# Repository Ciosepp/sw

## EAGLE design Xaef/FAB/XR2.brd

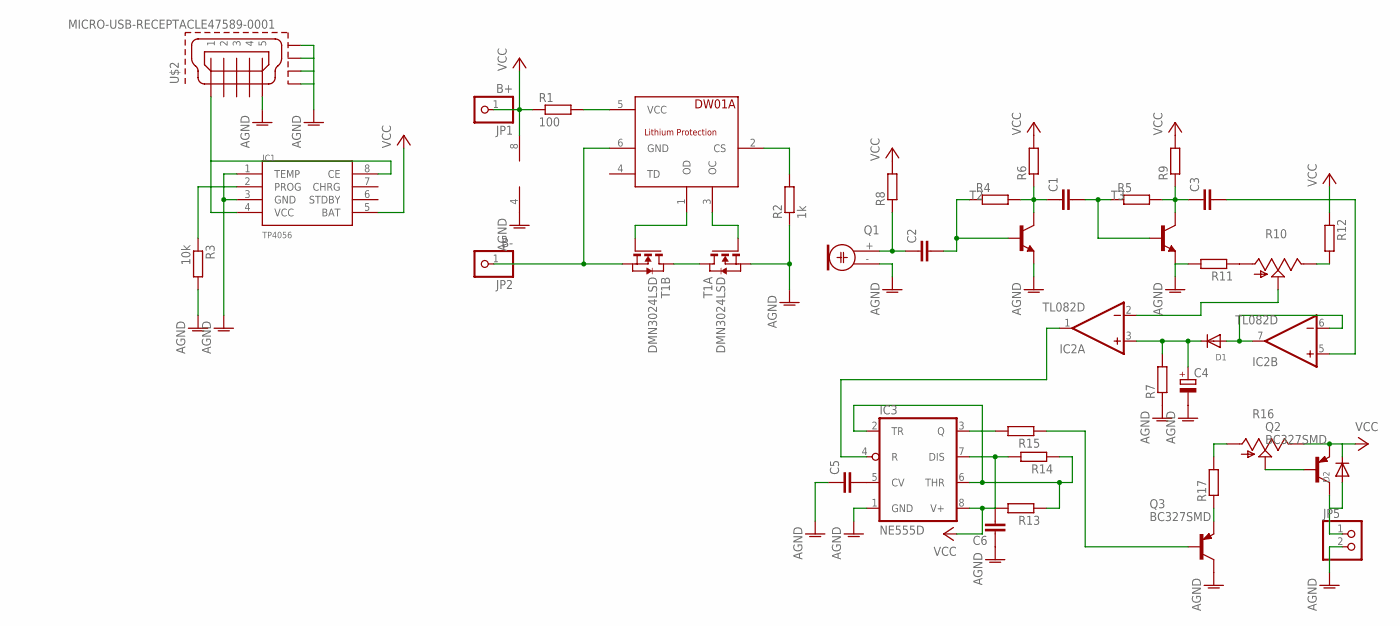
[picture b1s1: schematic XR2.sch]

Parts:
C1, C2, C3, C5, C6: C-EUC0603; C0603
C4: CPOL-EU153CLV-0605; 153CLV-0605
D1, D2: DIODESOT23_REFLOW; SOT23-R
IC1: TP4056; SOP-8
IC2: TL082D; SO08
IC3: NE555D; SO08
JP1: B+; 1X01
JP2: B-; 1X01
JP5: PINHD-1X2; 1X02
Q1: ELECTRET; 9.7ELECTRET
Q2, Q3: BC327SMD; SOT23-BEC
R1: 100; R0805
R2: 1k; R0805
R3: 10k; R0805
R4, R5, R6, R7, R8, R9, R11, R12, R13, R14, R15, R17: R-EU_R0603; R0603
R10, R16: TRIM_US-B25U; B25U
T1: DMN3024LSD; TSSOP-8
T2, T3: MMBT3904LT1-NPN-SOT23-BEC; SOT23-BEC
U$1: DW01A; SOT23-6
U$2: MICRO-USB-RECEPTACLE47589-0001; 47589-0001

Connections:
AGND: C4.-, C5.1, C6.1, IC1.1 (TEMP), IC1.3 (GND), IC2.4 (V-), IC3.1 (GND), JP5.2, Q1.- (1), Q3.C, R2.1, R3.2, R7.1, R11.2, T1.2 (S), T1.3 (S), T2.E, T3.E, U$2.5, U$2.CASING1 (GND1), U$2.CASING2 (GND2), U$2.CASING3 (GND3), U$2.CASING4 (GND4)
unnamed: T1.4 (G), U$1.3 (OC)
unnamed: T1.5 (G), U$1.1 (OD)
unnamed: T1.1 (D), T1.8 (D)
unnamed: R2.2, U$1.2 (CS)
unnamed: JP2.1, T1.6 (S), T1.7 (S), U$1.6 (GND)
unnamed: R1.2, U$1.5 (VCC)
unnamed: IC1.2 (PROG), R3.1
unnamed: IC2.2 (-IN), R10.S
unnamed: IC1.4 (VCC), IC1.8 (CE), U$2.1
unnamed: C2.1, Q1.+ (2), R8.1
unnamed: C2.2, R4.1, T2.B
unnamed: C1.1, R4.2, R6.1, T2.C
unnamed: C3.1, R5.2, R9.1, T3.C
unnamed: C1.2, R5.1, T3.B
unnamed: D1.1 (A), IC2.6 (-IN), IC2.7 (OUT)
unnamed: R10.A, R11.1
unnamed: C3.2, IC2.5 (+IN)
unnamed: C4.+, D1.3 (C), IC2.3 (+IN), R7.2
unnamed: R10.E, R12.2
unnamed: IC2.1 (OUT), IC3.4 (R)
unnamed: IC3.2 (TR), IC3.6 (THR), R13.1, R14.1
unnamed: C5.2, IC3.5 (CV)
unnamed: IC3.3 (Q), R15.2
unnamed: Q3.B, R15.1
unnamed: C6.2, IC3.7 (DIS), R14.2
unnamed: Q3.E, R17.1
unnamed: R16.A, R17.2
unnamed: Q2.B, R16.S
unnamed: D2.1 (A), JP5.1, Q2.C
VCC: D2.3 (C), IC1.5 (BAT), IC2.8 (V+), IC3.8 (V+), JP1.1, Q2.E, R1.1, R6.2, R8.2, R9.2, R12.1, R13.2, R16.E

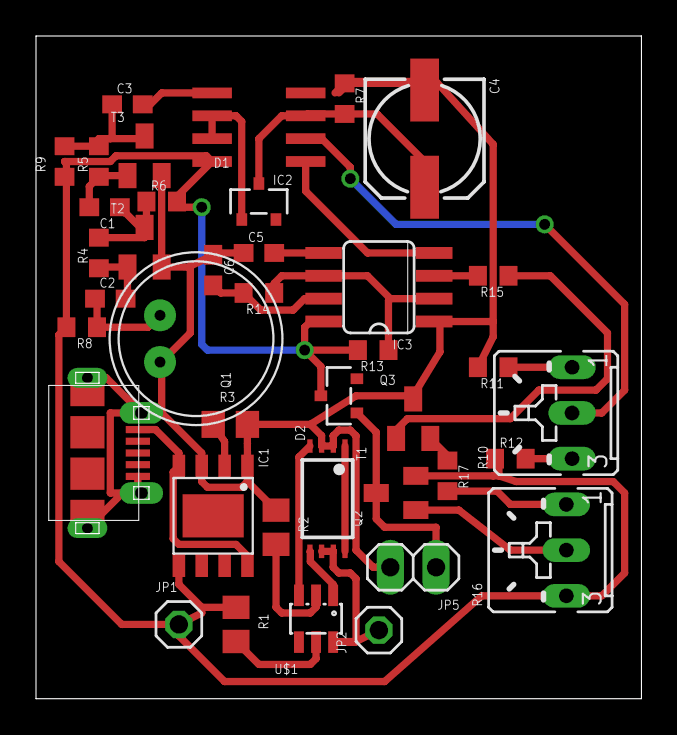
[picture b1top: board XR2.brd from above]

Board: 2 copper layers, 33.6 x 36.8 mm, 39 parts (0 on the bottom side), 31 nets.

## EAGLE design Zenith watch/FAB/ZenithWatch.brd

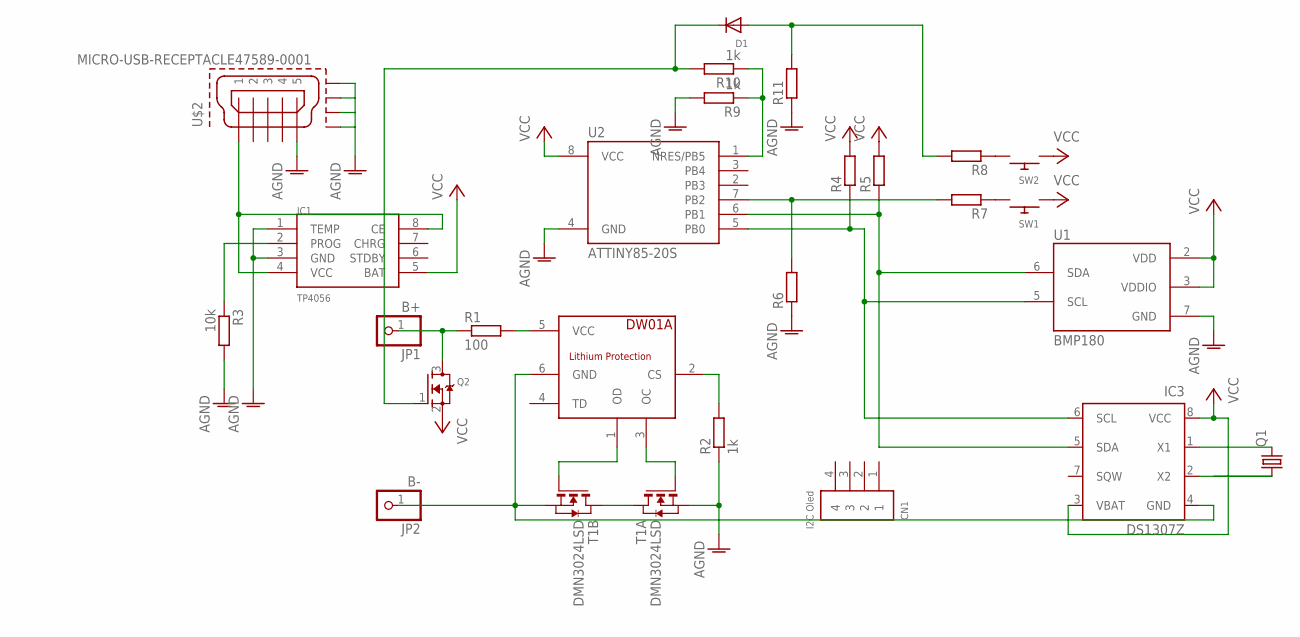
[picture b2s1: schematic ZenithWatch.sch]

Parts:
CN1: I2C Oled; 1X04-BIG
D1: DIODESOT23_REFLOW; SOT23-R
IC1: TP4056; SOP-8
IC3: DS1307Z; SOIC8
JP1: B+; 1X01
JP2: B-; 1X01
Q1: CRYSTALCTS406; CTS406
Q2: MOSFET-NREFLOW; SOT23
R1: 100; R0603
R2, R9, R10: 1k; R0603
R3: 10k; R0603
R4, R5, R6, R7, R8, R11: R-EU_R0603; R0603
SW1, SW2: SWITCH_PUSHBUTTONC&K_KSS; BTN_CK_KSS
T1: DMN3024LSD; TSSOP-8
U1: BMP180
U2: ATTINY85-20S; SOIC8_EIAJ_208MIL
U$1: DW01A; SOT23-6
U$2: MICRO-USB-RECEPTACLE47589-0001; 47589-0001

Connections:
AGND: IC1.1 (TEMP), IC1.3 (GND), R2.1, R3.2, R6.1, R9.2, R11.1, T1.2 (S), T1.3 (S), U1.7 (GND), U2.4 (GND), U$2.5, U$2.CASING1 (GND1), U$2.CASING2 (GND2), U$2.CASING3 (GND3), U$2.CASING4 (GND4)
unnamed: T1.4 (G), U$1.3 (OC)
unnamed: T1.5 (G), U$1.1 (OD)
unnamed: T1.1 (D), T1.8 (D)
unnamed: R2.2, U$1.2 (CS)
unnamed: IC3.4 (GND), JP2.1, T1.6 (S), T1.7 (S), U$1.6 (GND)
unnamed: R1.2, U$1.5 (VCC)
unnamed: IC1.2 (PROG), R3.1
unnamed: IC3.5 (SDA), R5.1, U1.6 (SDA), U2.6 (PB1)
unnamed: IC1.4 (VCC), IC1.8 (CE), U$2.1
unnamed: IC3.6 (SCL), R4.1, U1.5 (SCL), U2.5 (PB0)
unnamed: R7.1, SW1.P$2
unnamed: R8.1, SW2.P$2
unnamed: R6.2, R7.2, U2.7 (PB2)
unnamed: IC3.1 (X1), Q1.3 (2)
unnamed: IC3.2 (X2), Q1.1
unnamed: JP1.1, Q2.3 (D), R1.1
unnamed: R9.1, R10.1, U2.1 (NRES/PB5)
unnamed: D1.3 (C), Q2.1 (G), R10.2
unnamed: D1.1 (A), R8.2, R11.2
VCC: IC1.5 (BAT), IC3.3 (VBAT), IC3.8 (VCC), Q2.2 (S), R4.2, R5.2, SW1.P$1, SW2.P$1, U1.2 (VDD), U1.3 (VDDIO), U2.8 (VCC)

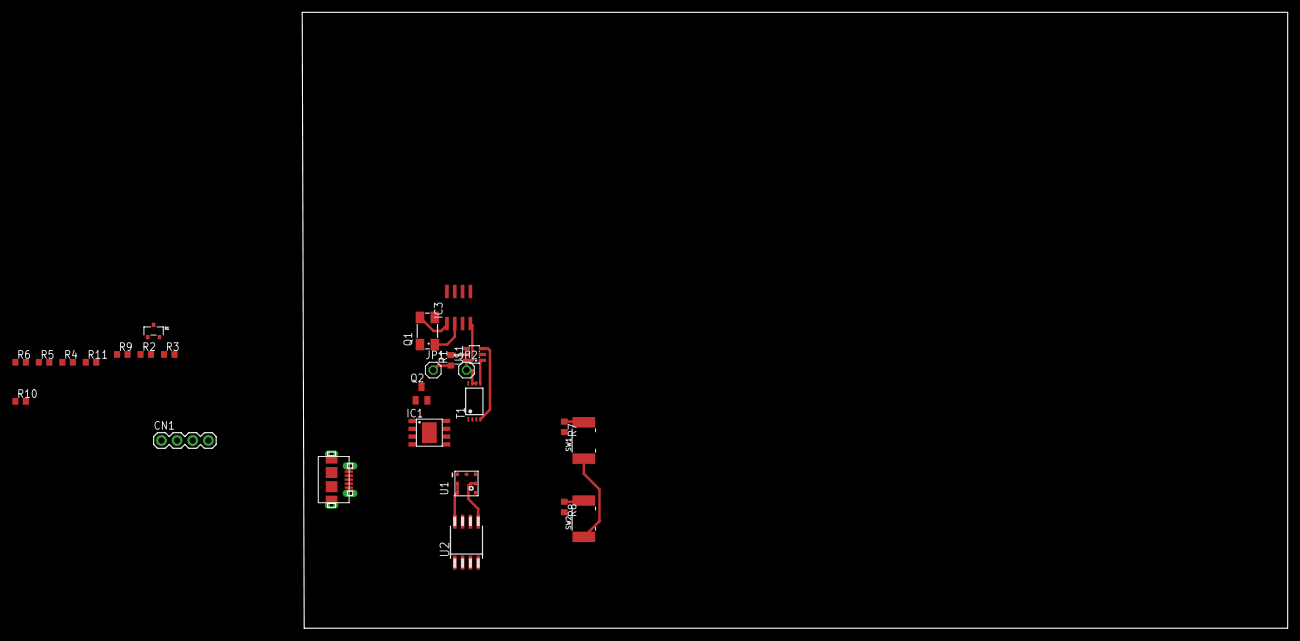
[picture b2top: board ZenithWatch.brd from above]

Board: 2 copper layers, 160.0 x 100.0 mm, 26 parts (0 on the bottom side), 21 nets.

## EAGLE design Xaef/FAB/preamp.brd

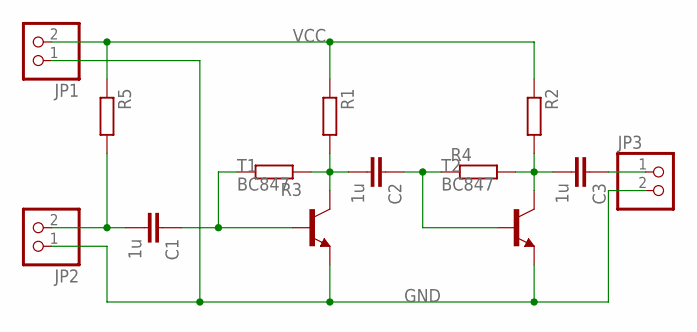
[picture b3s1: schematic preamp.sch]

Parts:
C1, C2, C3: 1u; C0805
JP1, JP2, JP3: PINHD-1X2; 1X02
R1, R2, R3, R4, R5: R-EU_R0805; R0805
T1, T2: BC847; SOT23

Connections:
GND: JP1.1, JP2.1, JP3.2, T1.2 (E), T2.2 (E)
unnamed: C1.2, JP2.2, R5.2
unnamed: C1.1, R3.2, T1.1 (B)
unnamed: C2.2, R1.2, R3.1, T1.3 (C)
unnamed: C2.1, R4.1, T2.1 (B)
unnamed: C3.2, R2.2, R4.2, T2.3 (C)
unnamed: C3.1, JP3.1
VCC: JP1.2, R1.1, R2.1, R5.1

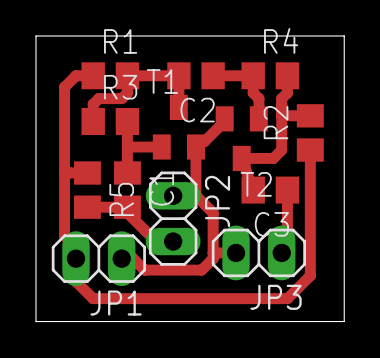
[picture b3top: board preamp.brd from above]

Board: 2 copper layers, 17.1 x 15.9 mm, 13 parts (0 on the bottom side), 8 nets.

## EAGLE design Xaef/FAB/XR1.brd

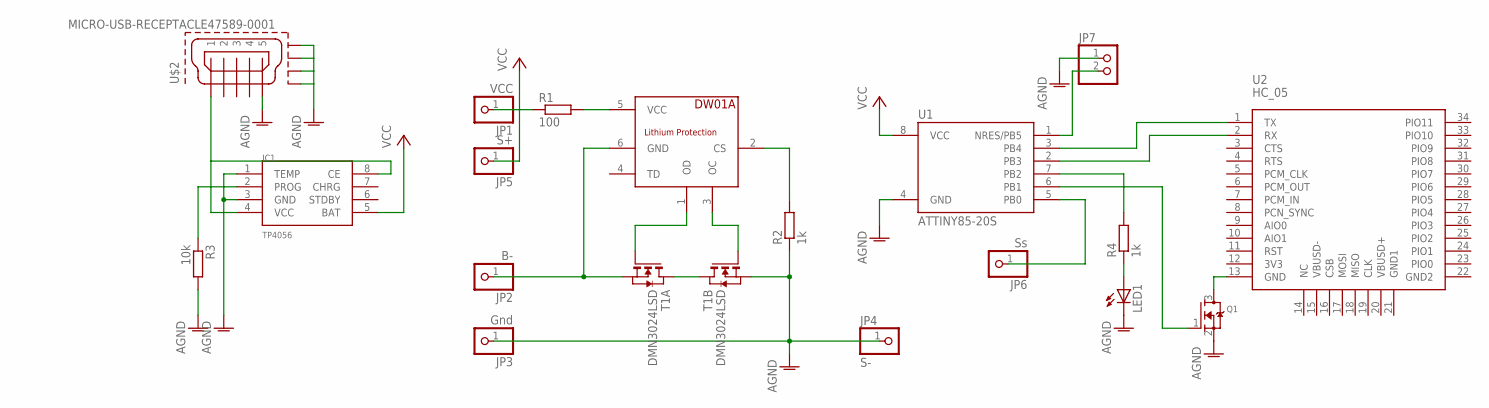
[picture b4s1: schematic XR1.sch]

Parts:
IC1: TP4056; SOP-8
JP1: VCC; 1X01
JP2: B-; 1X01
JP3: Gnd; 1X01
JP4: S-; 1X01
JP5: S+; 1X01
JP6: Ss; 1X01
JP7: PINHD-1X2; 1X02
LED1: LEDCHIP-LED0603; CHIP-LED0603
Q1: MOSFET-NREFLOW; SOT23
R1: 100; R0603
R2, R4: 1k; R0603
R3: 10k; R0603
T1: DMN3024LSD; TSSOP-8
U1: ATTINY85-20S; SOIC8_EIAJ_208MIL
U2: HC_05; BLUETOOTH_SMD
U$1: DW01A; SOT23-6
U$2: MICRO-USB-RECEPTACLE47589-0001; 47589-0001

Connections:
AGND: IC1.1 (TEMP), IC1.3 (GND), JP3.1, JP4.1, JP7.1, LED1.C, Q1.2 (S), R2.1, R3.2, T1.6 (S), T1.7 (S), U1.4 (GND), U$2.5, U$2.CASING1 (GND1), U$2.CASING2 (GND2), U$2.CASING3 (GND3), U$2.CASING4 (GND4)
unnamed: T1.4 (G), U$1.1 (OD)
unnamed: T1.5 (G), U$1.3 (OC)
unnamed: T1.1 (D), T1.8 (D)
unnamed: R2.2, U$1.2 (CS)
unnamed: JP2.1, T1.2 (S), T1.3 (S), U$1.6 (GND)
unnamed: R1.2, U$1.5 (VCC)
unnamed: IC1.2 (PROG), R3.1
unnamed: JP6.1, U1.5 (PB0)
unnamed: IC1.4 (VCC), IC1.8 (CE), U$2.1
unnamed: JP7.2, U1.1 (NRES/PB5)
unnamed: Q1.3 (D), U2.13 (GND)
unnamed: Q1.1 (G), U1.6 (PB1)
unnamed: U1.3 (PB4), U2.1 (TX)
unnamed: U1.2 (PB3), U2.2 (RX)
unnamed: R4.2, U1.7 (PB2)
unnamed: LED1.A, R4.1
VCC: IC1.5 (BAT), JP1.1, JP5.1, R1.1, U1.8 (VCC)

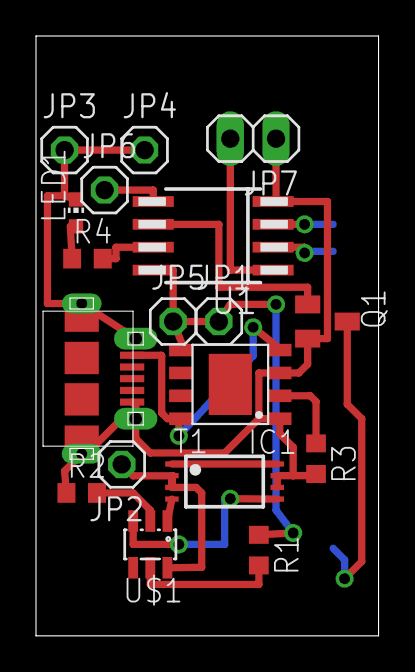
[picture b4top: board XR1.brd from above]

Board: 2 copper layers, 19.0 x 33.3 mm, 19 parts (1 on the bottom side), 18 nets.

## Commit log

2022-03-29 updated data hierarchy
2022-03-29 Included libraries and more files
2022-06-07 più nixiee!!!
2022-08-10 Auto stash before rebase of "origin/master"
2022-12-12 Tweaks
    Added description to Monophono SRC V0.0
2022-12-12 Nixie stuff has its own repo now
2022-12-12 Cleaning
2023-02-12 Auto stash before merge of "master" and "origin/master"

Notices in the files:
parts and their libraries:
con-molex-usb: (C) 2014 Tomasz Boleslaw CEDRO, cederom@tlen.pl, http://www.tomek.cedro.info.
